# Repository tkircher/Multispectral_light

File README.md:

# Multispectral_light
This is a board full of LEDs of various wavelengths. Inspired by Ben Krasnow.

This PCB is a single-layer version I had manufactured on an aluminum substrate.

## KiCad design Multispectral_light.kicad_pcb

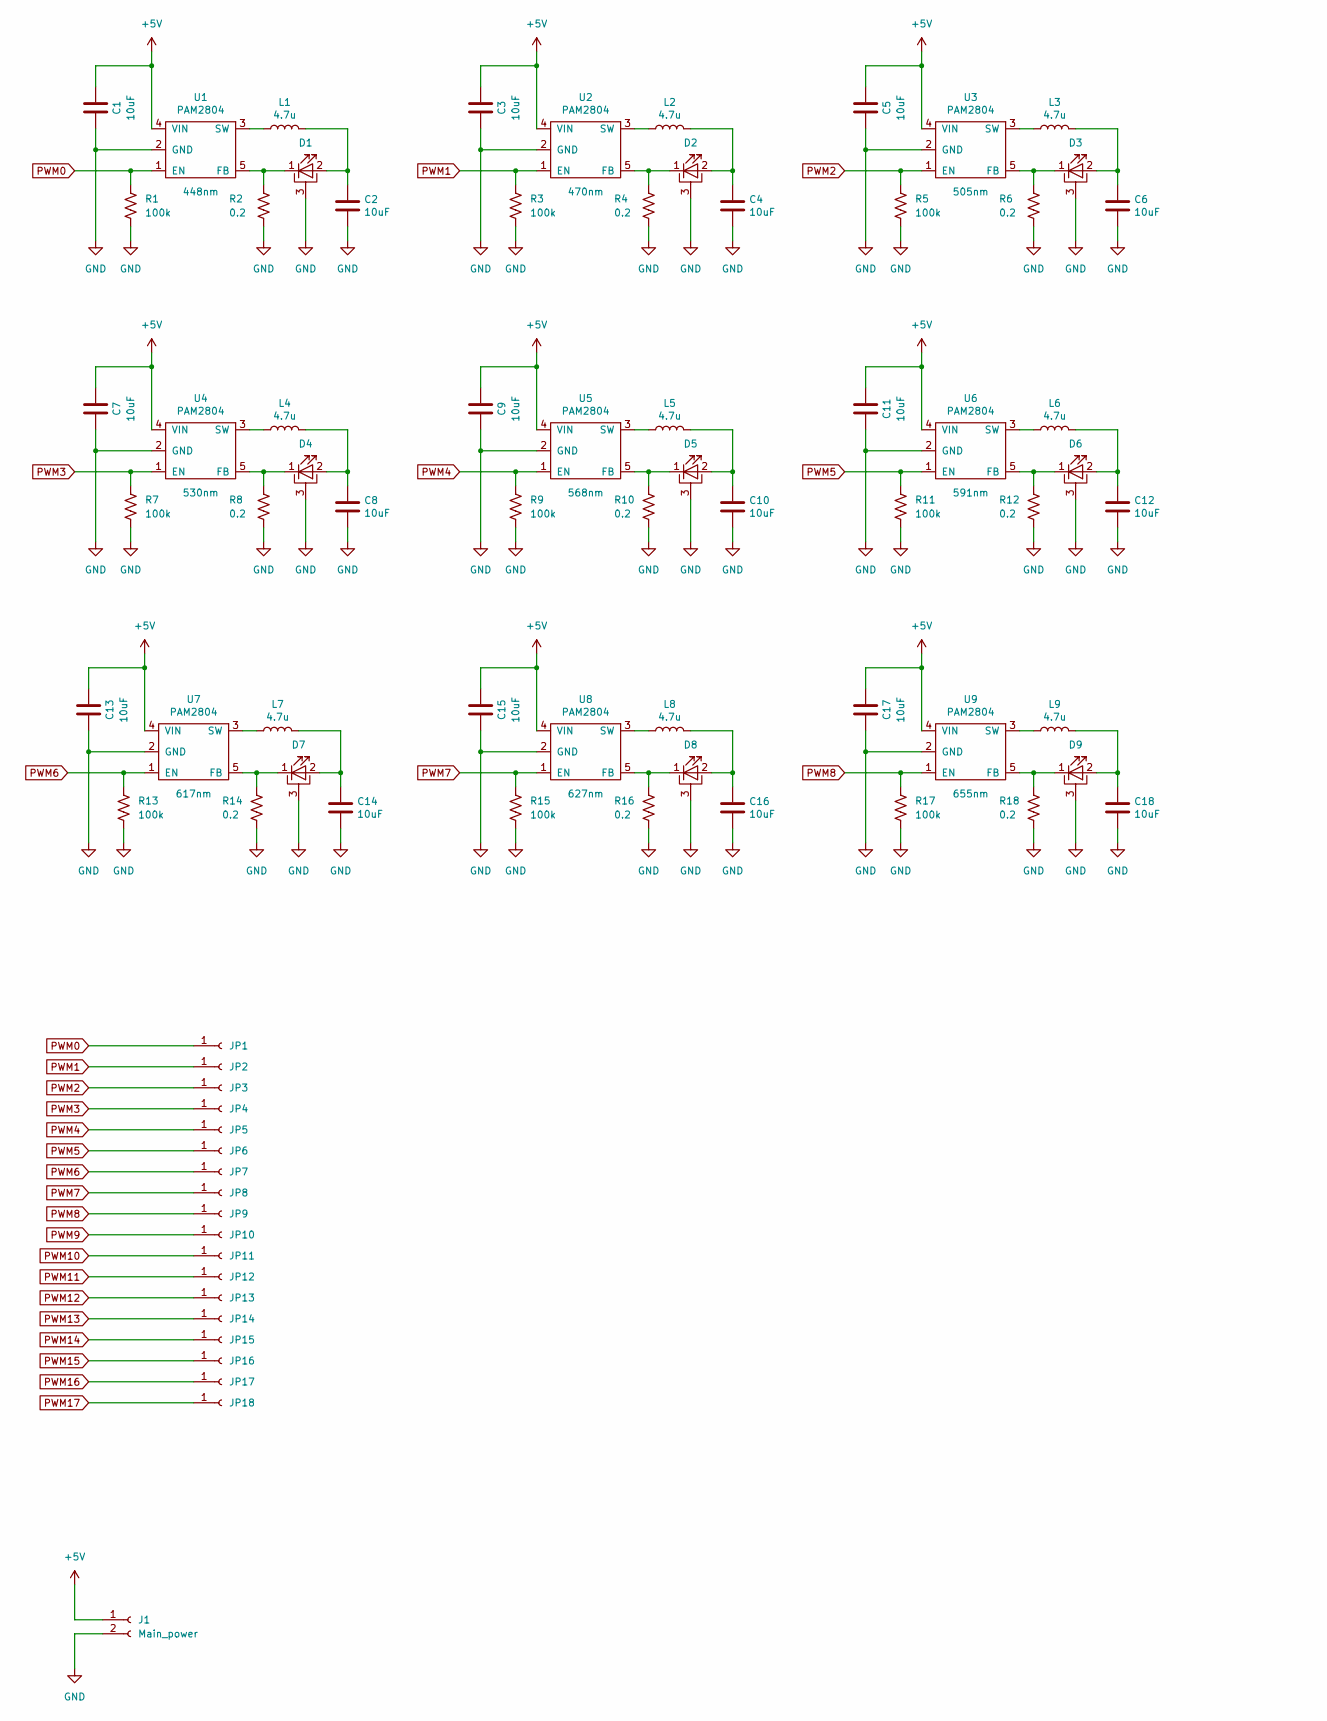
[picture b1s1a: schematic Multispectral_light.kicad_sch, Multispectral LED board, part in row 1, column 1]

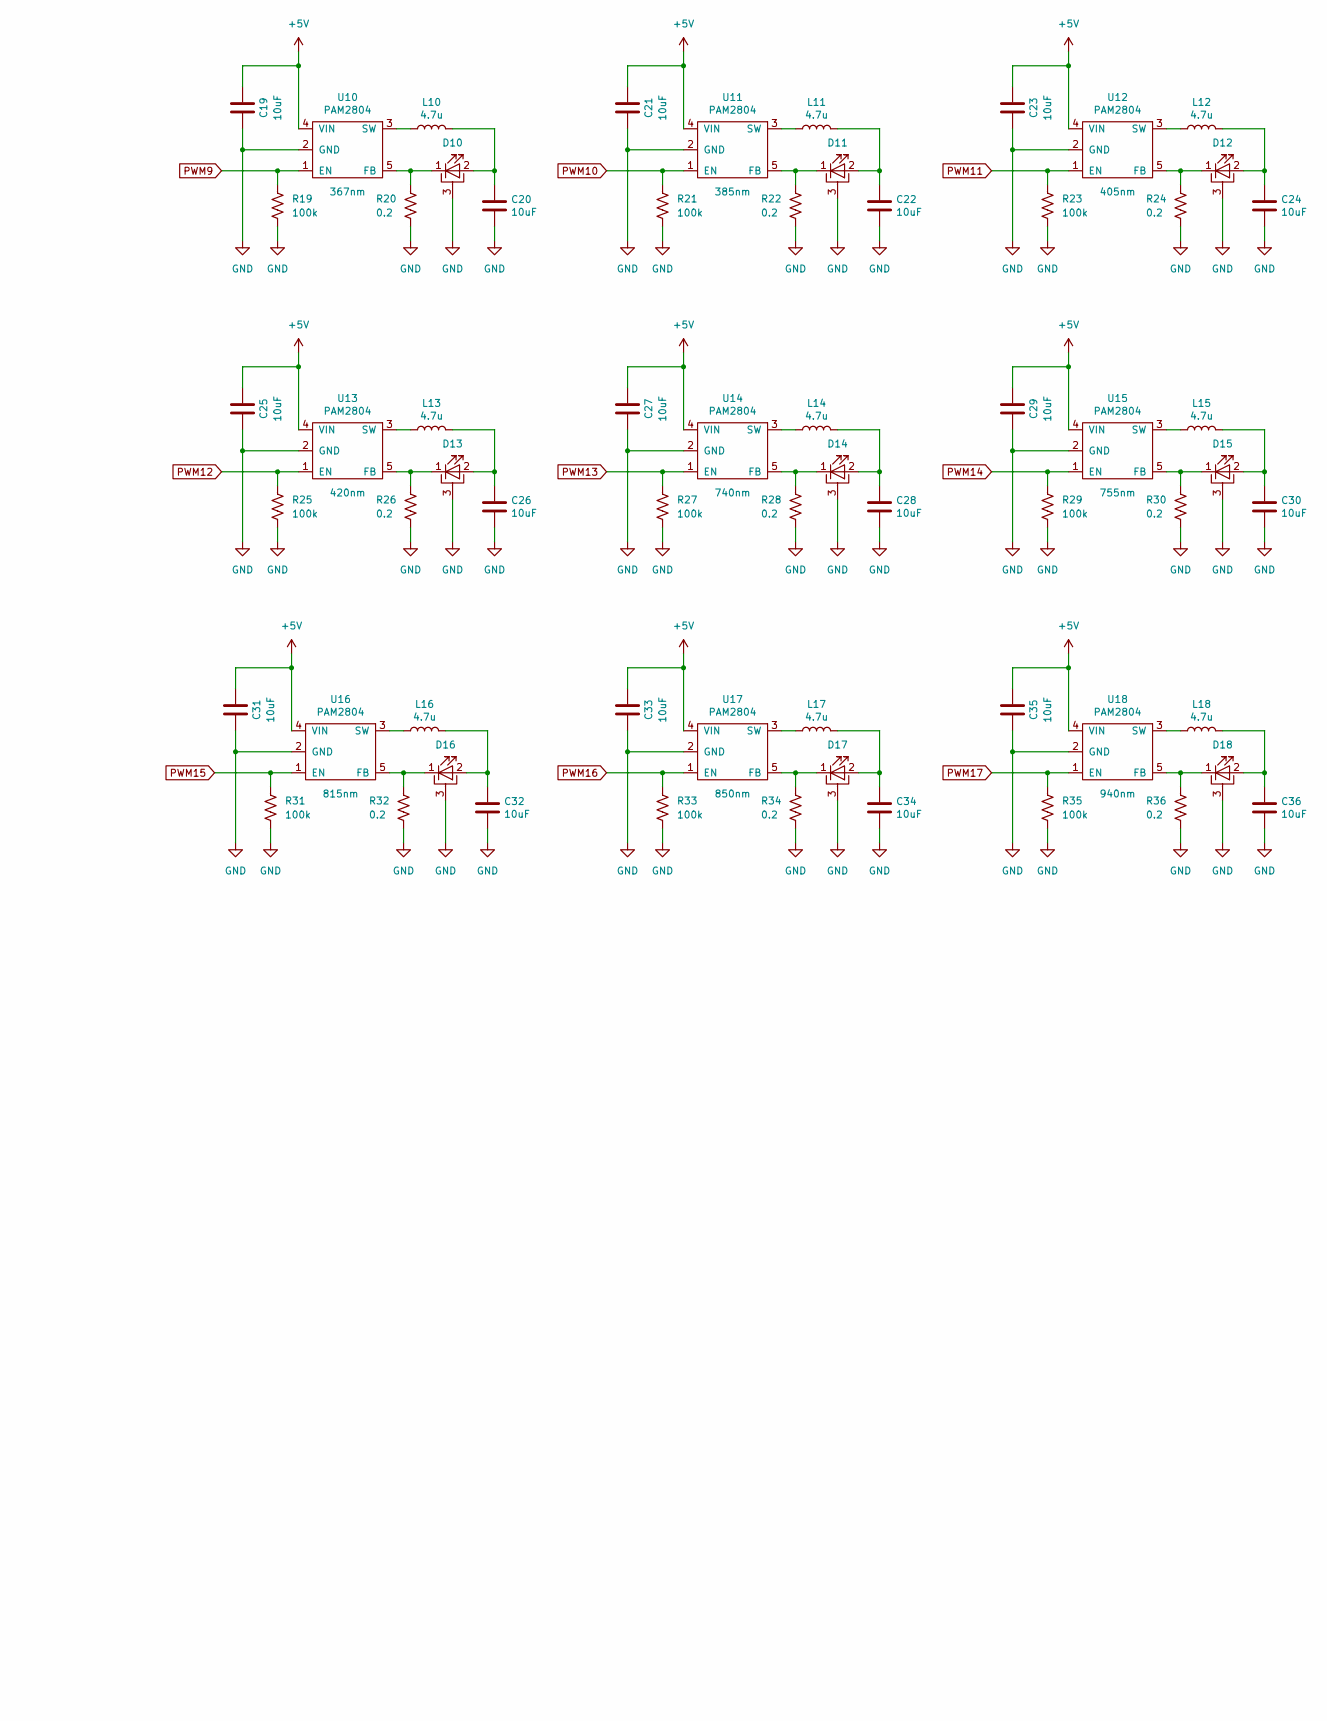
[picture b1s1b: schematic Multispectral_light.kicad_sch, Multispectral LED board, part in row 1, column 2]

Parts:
C1, C2, C3, C4, C5, C6, C7, C8, C9, C10, C11, C12, C13, C14, C15, C16, C17, C18, C19, C20, C21, C22, C23, C24, C25, C26, C27, C28, C29, C30, C31, C32, C33, C34, C35, C36: 10uF; C_0805_2012Metric; Digikey Part Number 490-3886-1-ND
D1: 448nm; LuxeonRebelColor; Digikey Part Number 1416-1026-1-ND
D2: 470nm; LuxeonRebelColor; Digikey Part Number 1416-1026-1-ND
D3: 505nm; LuxeonRebelColor; Digikey Part Number 1416-1026-1-ND
D4: 530nm; LuxeonRebelColor; Digikey Part Number 1416-1026-1-ND
D5: 568nm; LuxeonRebelColor; Digikey Part Number 1416-1026-1-ND
D6: 591nm; LuxeonRebelColor; Digikey Part Number 1416-1026-1-ND
D7: 617nm; LuxeonRebelColor; Digikey Part Number 1416-1026-1-ND
D8: 627nm; LuxeonRebelColor; Digikey Part Number 1416-1026-1-ND
D9: 655nm; LuxeonRebelColor; Digikey Part Number 1416-1026-1-ND
D10: 367nm; SeoulViosys_CUN6GF1A; Digikey Part Number 1416-1026-1-ND
D11: 385nm; Everlight_ELUA3535; Digikey Part Number 1416-1026-1-ND
D12: 405nm; Everlight_ELUA3535; Digikey Part Number 1416-1026-1-ND
D13: 420nm; SeoulViosys_CUN6GF1A; Digikey Part Number 1416-1026-1-ND
D14: 740nm; QT_Brightek_QBHP684; Digikey Part Number 1416-1026-1-ND
D15: 755nm; Stanley_FWR; Digikey Part Number 1416-1026-1-ND
D16: 815nm; Luminus_B90H; Digikey Part Number 1416-1026-1-ND
D17: 850nm; QT_Brightek_QBHP684; Digikey Part Number 1416-1026-1-ND
D18: 940nm; QT_Brightek_QBHP684; Digikey Part Number 1416-1026-1-ND
J1: Main_power; Power_SMD_edge
JP1, JP2, JP3, JP4, JP5, JP6, JP7, JP8, JP9, JP10, JP11, JP12, JP13, JP14, JP15, JP16, JP17, JP18: Conn_01x01_Female; SolderWirePad_1x01_SMD_1x2mm
L1, L2, L3, L4, L5, L6, L7, L8, L9, L10, L11, L12, L13, L14, L15, L16, L17, L18: 4.7u; L_1007_2518Metric; Digikey Part Number 587-1621-1-ND
R1, R3, R5, R7, R9, R11, R13, R15, R17, R19, R21, R23, R25, R27, R29, R31, R33, R35: 100k; R_0805_2012Metric
R2, R4, R6, R8, R10, R12, R14, R16, R18, R20, R22, R24, R26, R28, R30, R32, R34, R36: 0.2; R_0805_2012Metric
U1, U2, U3, U4, U5, U6, U7, U8, U9, U10, U11, U12, U13, U14, U15, U16, U17, U18: PAM2804; SOT-23-5; Digikey Part Number PAM2804AAB010DICT-ND

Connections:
+5V: C1.2, C3.2, C5.2, C7.2, C9.2, C11.2, C13.2, C15.2, C17.2, C19.2, C21.2, C23.2, C25.2, C27.2, C29.2, C31.2, C33.2, C35.2, J1.1, U1.4 (VIN), U2.4 (VIN), U3.4 (VIN), U4.4 (VIN), U5.4 (VIN), U6.4 (VIN), U7.4 (VIN), U8.4 (VIN), U9.4 (VIN), U10.4 (VIN), U11.4 (VIN), U12.4 (VIN), U13.4 (VIN), U14.4 (VIN), U15.4 (VIN), U16.4 (VIN), U17.4 (VIN), U18.4 (VIN)
GND: C1.1, C2.2, C3.1, C4.2, C5.1, C6.2, C7.1, C8.2, C9.1, C10.2, C11.1, C12.2, C13.1, C14.2, C15.1, C16.2, C17.1, C18.2, C19.1, C20.2, C21.1, C22.2, C23.1, C24.2, C25.1, C26.2, C27.1, C28.2, C29.1, C30.2, C31.1, C32.2, C33.1, C34.2, C35.1, C36.2, D1.3 (PAD), D2.3 (PAD), D3.3 (PAD), D4.3 (PAD), D5.3 (PAD), D6.3 (PAD), D7.3 (PAD), D8.3 (PAD), D9.3 (PAD), D10.3 (PAD), D11.3 (PAD), D12.3 (PAD), D13.3 (PAD), D14.3 (PAD), D15.3 (PAD), D16.3 (PAD), D17.3 (PAD), D18.3 (PAD), J1.2, R1.2, R2.2, R3.2, R4.2, R5.2, R6.2, R7.2, R8.2, R9.2, R10.2, R11.2, R12.2, R13.2, R14.2, R15.2, R16.2, R17.2, R18.2, R19.2, R20.2, R21.2, R22.2, R23.2, R24.2, R25.2, R26.2, R27.2, R28.2, R29.2, R30.2, R31.2, R32.2, R33.2, R34.2, R35.2, R36.2, U1.2 (GND), U2.2 (GND), U3.2 (GND), U4.2 (GND), U5.2 (GND), U6.2 (GND), U7.2 (GND), U8.2 (GND), U9.2 (GND), U10.2 (GND), U11.2 (GND), U12.2 (GND), U13.2 (GND), U14.2 (GND), U15.2 (GND), U16.2 (GND), U17.2 (GND), U18.2 (GND)
unnamed: C2.1, D1.2 (A), L1.2
unnamed: C4.1, D2.2 (A), L2.2
unnamed: C6.1, D3.2 (A), L3.2
unnamed: C8.1, D4.2 (A), L4.2
unnamed: C10.1, D5.2 (A), L5.2
unnamed: C12.1, D6.2 (A), L6.2
unnamed: C14.1, D7.2 (A), L7.2
unnamed: C16.1, D8.2 (A), L8.2
unnamed: C18.1, D9.2 (A), L9.2
unnamed: C20.1, D10.2 (A), L10.2
unnamed: C22.1, D11.2 (A), L11.2
unnamed: C24.1, D12.2 (A), L12.2
unnamed: C26.1, D13.2 (A), L13.2
unnamed: C28.1, D14.2 (A), L14.2
unnamed: C30.1, D15.2 (A), L15.2
unnamed: C32.1, D16.2 (A), L16.2
unnamed: C34.1, D17.2 (A), L17.2
unnamed: C36.1, D18.2 (A), L18.2
unnamed: D1.1 (K), R2.1, U1.5 (FB)
unnamed: D2.1 (K), R4.1, U2.5 (FB)
unnamed: D3.1 (K), R6.1, U3.5 (FB)
unnamed: D4.1 (K), R8.1, U4.5 (FB)
unnamed: D5.1 (K), R10.1, U5.5 (FB)
unnamed: D6.1 (K), R12.1, U6.5 (FB)
unnamed: D7.1 (K), R14.1, U7.5 (FB)
unnamed: D8.1 (K), R16.1, U8.5 (FB)
unnamed: D9.1 (K), R18.1, U9.5 (FB)
unnamed: D10.1 (K), R20.1, U10.5 (FB)
unnamed: D11.1 (K), R22.1, U11.5 (FB)
unnamed: D12.1 (K), R24.1, U12.5 (FB)
unnamed: D13.1 (K), R26.1, U13.5 (FB)
unnamed: D14.1 (K), R28.1, U14.5 (FB)
unnamed: D15.1 (K), R30.1, U15.5 (FB)
unnamed: D16.1 (K), R32.1, U16.5 (FB)
unnamed: D17.1 (K), R34.1, U17.5 (FB)
unnamed: D18.1 (K), R36.1, U18.5 (FB)
unnamed: L1.1, U1.3 (SW)
unnamed: L2.1, U2.3 (SW)
unnamed: L3.1, U3.3 (SW)
unnamed: L4.1, U4.3 (SW)
unnamed: L5.1, U5.3 (SW)
unnamed: L6.1, U6.3 (SW)
unnamed: L7.1, U7.3 (SW)
unnamed: L8.1, U8.3 (SW)
unnamed: L9.1, U9.3 (SW)
unnamed: L10.1, U10.3 (SW)
unnamed: L11.1, U11.3 (SW)
unnamed: L12.1, U12.3 (SW)
unnamed: L13.1, U13.3 (SW)
unnamed: L14.1, U14.3 (SW)
unnamed: L15.1, U15.3 (SW)
unnamed: L16.1, U16.3 (SW)
unnamed: L17.1, U17.3 (SW)
unnamed: L18.1, U18.3 (SW)
PWM0: JP1.1, R1.1, U1.1 (EN)
PWM1: JP2.1, R3.1, U2.1 (EN)
PWM2: JP3.1, R5.1, U3.1 (EN)
PWM3: JP4.1, R7.1, U4.1 (EN)
PWM4: JP5.1, R9.1, U5.1 (EN)
PWM5: JP6.1, R11.1, U6.1 (EN)
PWM6: JP7.1, R13.1, U7.1 (EN)
PWM7: JP8.1, R15.1, U8.1 (EN)
PWM8: JP9.1, R17.1, U9.1 (EN)
PWM9: JP10.1, R19.1, U10.1 (EN)
PWM10: JP11.1, R21.1, U11.1 (EN)
PWM11: JP12.1, R23.1, U12.1 (EN)
PWM12: JP13.1, R25.1, U13.1 (EN)
PWM13: JP14.1, R27.1, U14.1 (EN)
PWM14: JP15.1, R29.1, U15.1 (EN)
PWM15: JP16.1, R31.1, U16.1 (EN)
PWM16: JP17.1, R33.1, U17.1 (EN)
PWM17: JP18.1, R35.1, U18.1 (EN)

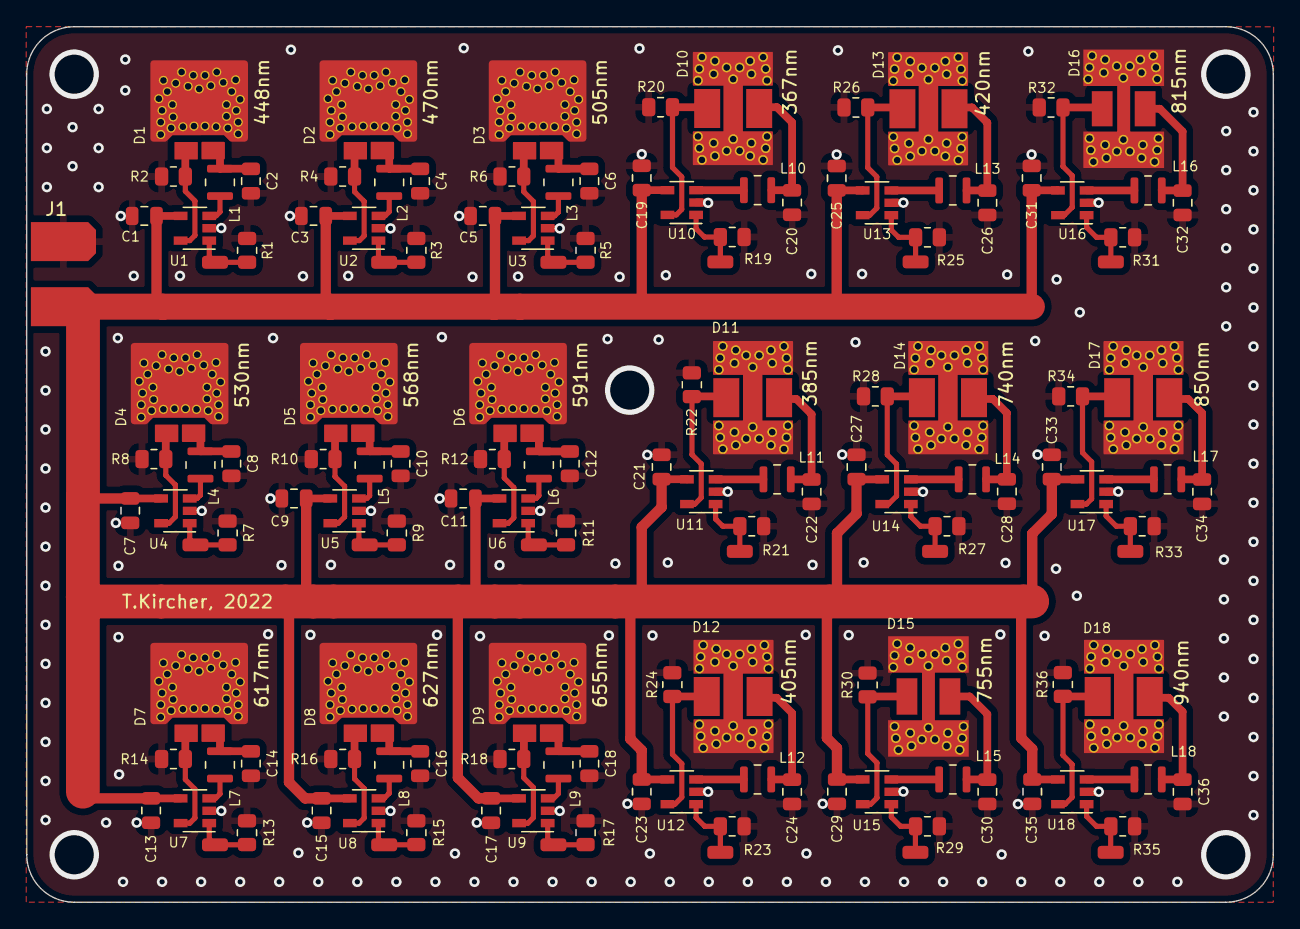
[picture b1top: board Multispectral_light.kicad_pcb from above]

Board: 2 copper layers, 95.8 x 67.3 mm, 145 parts (0 on the bottom side), 74 nets.
